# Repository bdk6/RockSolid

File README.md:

# RockSolid
Oven controlled quartz oscillator(s).

RockSolid is a cheap, easy to build, custom Oven Controlled Crystal
Oscillator (OCXO.)  You can build it for under $10 US, including having
the PCB made.  You can build it for the exact frequency you need.

## Credit
A significant amount of credit goes to someone on the web that I can't
find again.  I was in the process of designing a "simple" crystal oven
thought about doing something similar to how RockSolid works.  But what
I had was still considerably more complicated.  I found this basic circuit
on the web and was impressed.  I modified it a small amount and used it
in RockSolid.  As soon as I can find the website and name, I will be sure
to update that here.

## What's an OXCO and why do we need it?
Quartz crystal oscillators are known for being accurate.  And they are.
But, in general, not nearly as most people might think.  Go to your
favorite parts distributor website and look at crystals.  Under "tolerance"
you will find various numbers mostly from about 10 to 100 ppm.  That's
"Parts Per Million."  Let's settle on 100 for this discussion.  For each
one million "parts" there can be a variation of plus or minus 100.  In our
case the "parts" are "Hertz" of the oscillation.  For a 1 MHz crystal, the
error could be plus or minus 100 Hz.  For a 2 MHz crystal, it could be
2 times 100, or plus or minus 200 Hz.  Even though this way of specifying
it is a bit confusing at first, it turns out to be convenient.  It is, in
essence, another way of saying percentage.  Parts Per Million is a ratio,
 Parts / Million.  So, 100 ppm  is equal to 100 / 1,000,000 = 1/10,000
  = 0.01%.

It's imporant to remember that the specified 100 ppm is ONLY for the
crystal.  That means that the circuit can affect that even more.  But even
with a perfect circuit that doesn't add any more error (good luck!)
plugging in a different crystal can affect the frequency  as much as
200 ppm (remember it's plus or minus, so if the first one was plus 100
and the next was minus 100 the difference is 200 ppm.)  Of course, the
rest of the circuit is going to have its say, too.  So our error can be
considerably more than the crystal spec.

What does 100ppm mean in the real world?  It sounds pretty small.  Will
we even notice?  Let's take two examples.  A clock and a radio.

Let's build a "thought experiment" clock.  We start with a 1 MHz crystal
and divide it down to 1 Hz to count seconds.  There are 86400
(60 sec/min * 60 min/hr * 24 hr / day) in a day.  In a 30 day month, there
are 30 * 86400 or 2,592,000 seconds.

But our crystal is "fast" by 100 ppm.  So instead of 1,000,000 oscillations
per second it actually oscillates 1,000,100 times per second.  When we
divide that by 1,000,000 to get 1 Hz, we actually get 1.0001 Hz.  Doesn't
look like much, does it.  But, what we think is 1 second is actually
1/1.0001 second.  And if we count 86,400 of those for a day, we get
86,400 over 1.0001 seconds, which is about 86,391 seconds.  At the end of
one day our clock is off by almost 9 seconds!  How about a month?  Let's
divide 2,592,000 / 1.0001 = 2,591,740.  After a month our clock is off by
260 seconds!  Two minutes and 20 seconds!  A good quality, ancient,
wind-up wristwatch was often better than that.  And after a year it will
be off by over half an hour.  Maybe not so accurate.

How about a radio?  A "two meter" (144 to 148 MHz) amateur band fm radio
uses "channels" that are spaced 5 KHz apart.  Let's say we build a
crystal oscillator to work on the channel from 145,000,000 to 145,005,000
Hz.  We use a crystal at 145,000,000 Hz (those don't really exist, but
let's pretend they do.)  It is spec'ed as +- 100 ppm.  At 145 million Hz
that means plus or minus 145 * 100 = 14,500 Hz!  We could be in any one of
SIX different channels other than the one we intend!  Anywhere from
144,985,500 to 145,014,500 Hz!

So, what do we do?  First, buy a better crystal.  But don't go overboard.
They get expensive pretty quick and that still won't solve the problem
completely.  Keep in mind there are two different specs on the crystal.
One is the tolerance, which means in a perfect circuit it could be off
that much.  The other is stability.  Once you get it working how much
will the frequency vary over time.
Take a look at the datasheet for any decent quality crystal
that you can find.  There will usually be a graph showing frequency vs
temperature.  It will be an upside down parabola, with the peak at
some particular temperature.  That peak will usually be right at the
specified frequency.

So we see that the crystal frequency varies with temperature.  If we get
everything else set just right and keep the crystal temperature regulated,
we can make it quite accurate and stable.  The peak of that parabola,
though, is usually specified at 25 C.  That's about room temperature.  Do
we need a heater and air conditioner?  Not necessarily.

There are other factors.  I've alluded to them a few times.  The frequency
the crystal oscillates at has a lot to do with the circuit it is in.
Especially the capacitance of that circuit.  We can vary the capacitance
of the circuit and adjust the frequency.  We can usually cover a pretty
wide range of frequencies that way.  Heating a circuit is pretty easy;
we do that all the time, like it or not.  Cooling is not so easy.  So,
let's heat the circuit up to some temperature above anything it might
encounter naturally.  Say 35 to 40 C.  And keep it stable.  Now, adjust
the rest of the circuit right on frequency at that temperature.  It will
now be MUCH more stable.  The better the quality of the components used,
the more stable and accurate it will be.  But even with rather cheap
parts it will be drastically improved.  You won't get NIST lab quality
from a ten cent crystal and cheap ebay capacitors, but you can get to or
below 1 ppm!

This temperature controlled oscillator is called an Oven Controlled
Crystal Oscillator or OXCO.

And THAT is what RockSolid is all about.  It's a crystal oscillator and
temperature regulating circuit, housed in a well-insulated environment
to get decent accuracy from a crystal oscillator.

## History

## The Goal and the Circuit
My ultimate goal for this project is a 0.1 frequency reference.  With
good quality parts and some work, I think that's achievable.  We'll see.
Even with really cheap parts from Chinal totalling less than $2 I think
we can get 1 ppm.  And this is small and cheap enough to build that you
can use it in various projects without adding much cost or too much space.
One ppm is often plenty good enough.  It gets you a clock accurate to
better than 3 seconds a month.  Or a radio that's close enough on
frequency.  Or a frequency counter that's off by no more than 10 Hz when
measuring a 10 Mhz signal.  It would have been considered lab quality
not TOO long ago.

The circuit is simple and cheap.  A standard 74HC04 CMOS hex inverter is
used as the active device.  The crystal and its capacitors are added
to build an oscillator.  The voltage to the oscillator is regulated
internally by a 78L05 regulator kept at the same temperature.  Voltage
will affect the frequency, too.  By keeping the regulator temperature
regulated, it is much more accurate.  For the same reason, it has a
near-constant load.  So the 5V may be off a little, but it should stay
quite stable.  Stability is the key.  We can adjust for inaccuracy, as
long as it stays stable.  The heater circuit consists of a power MOSFET
and two power resistors as heaters.  The MOSFET is controlled by a
divider circuit with a potentiometer and a thermistor.  As the thermistor
heats up, it cuts down drive to the MOSFET, decreasing the heating.  As
it cools, it increases the drive and heating.  The feedback stabilizes
the temperature, and we build the whole thing to spread the heat evenly
and be well-insulated from the outside world.  The heater and five volt
regulator are fed from an external, regulated 12 volt supply.

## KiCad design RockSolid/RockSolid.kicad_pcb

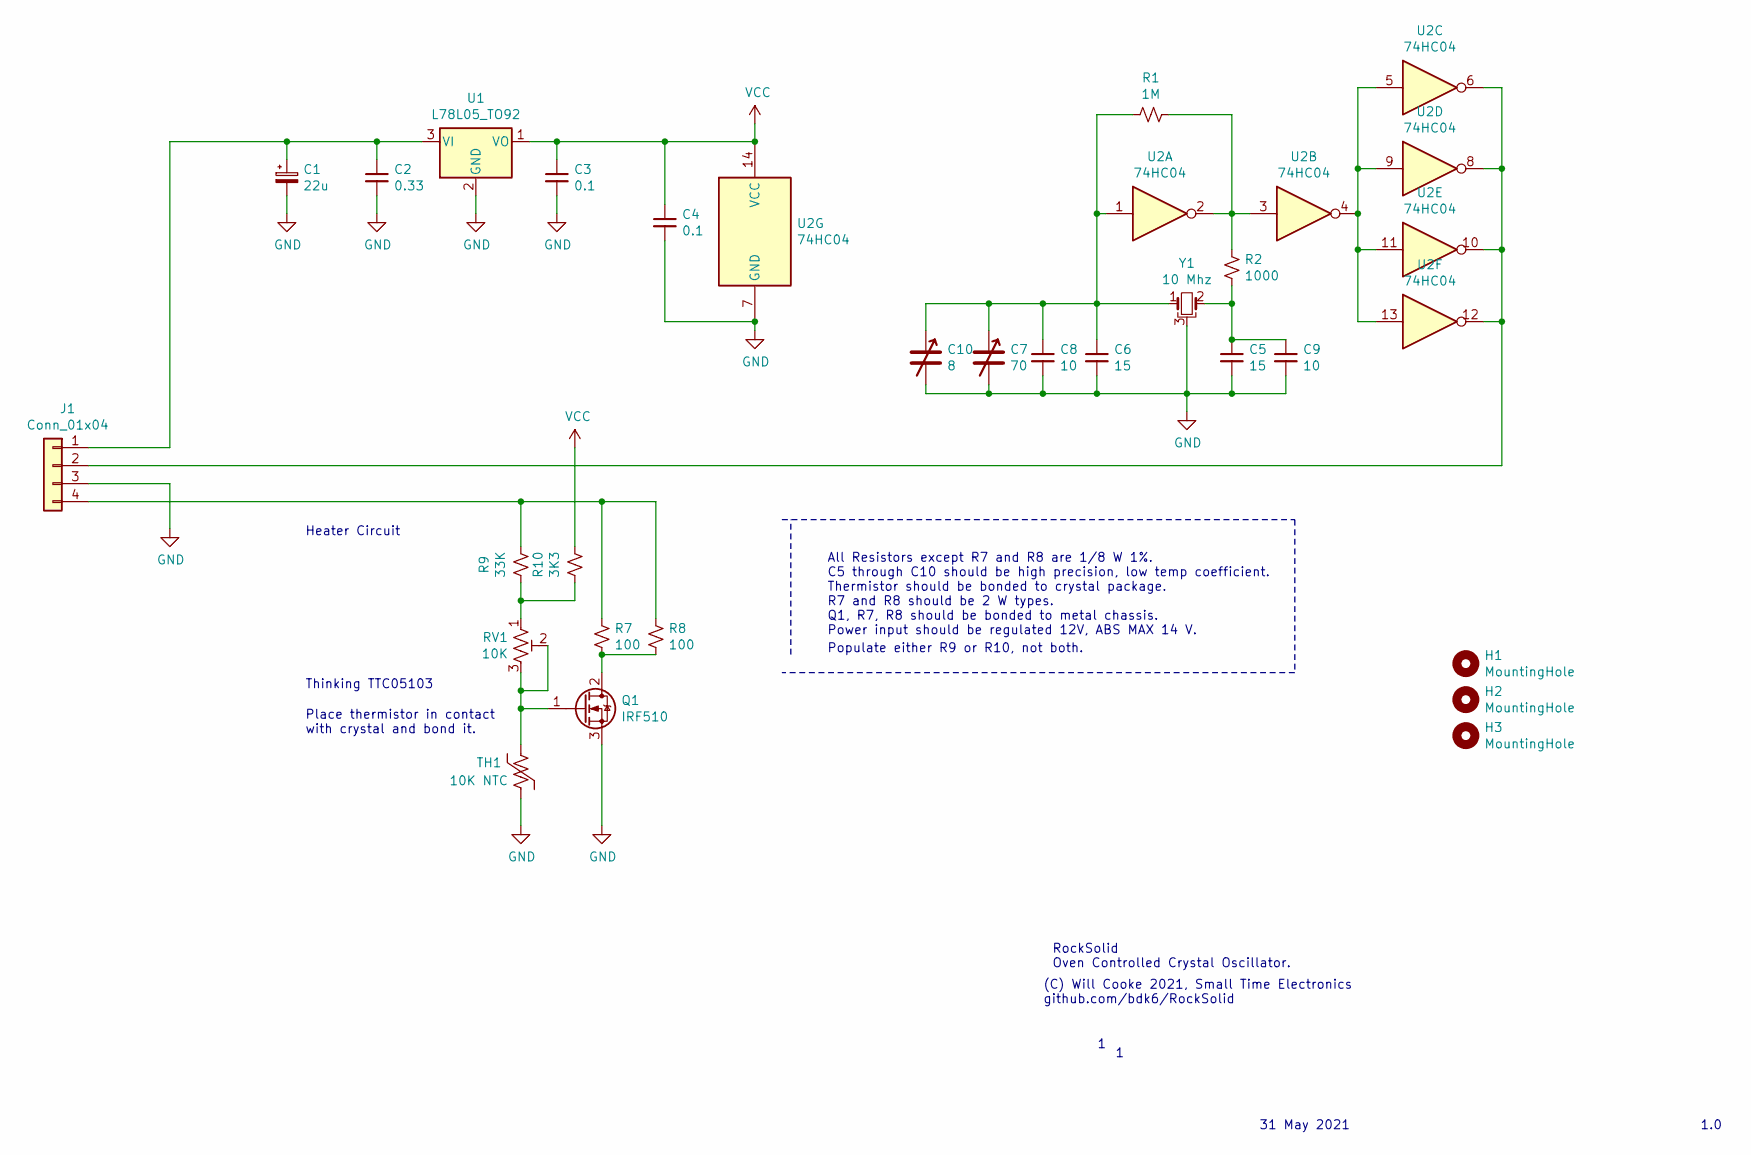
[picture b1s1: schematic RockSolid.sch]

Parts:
C1: 22u; CP_Radial_D5.0mm_P2.00mm
C2: 0.33; C_Disc_D4.7mm_W2.5mm_P5.00mm
C3, C4: 0.1; C_Disc_D4.7mm_W2.5mm_P5.00mm
C5, C6: 15; C_Disc_D4.7mm_W2.5mm_P5.00mm
C7: 70; C_Trimmer_6mm_2pin_5mm
C8, C9: 10; C_Disc_D4.7mm_W2.5mm_P5.00mm
C10: 8; C_Trimmer_6mm_2pin_5mm
H1, H2, H3: MountingHole; MountingHole_2.5mm
J1: Conn_01x04; PinHeader_1x04_P2.54mm_Vertical
Q1: IRF510; TO-220-3_Vertical
R1: 1M; R_Axial_DIN0207_L6.3mm_D2.5mm_P7.62mm_Horizontal
R2: 1000; R_Axial_DIN0207_L6.3mm_D2.5mm_P7.62mm_Horizontal
R7, R8: 100; R_Axial_DIN0617_L17.0mm_D6.0mm_P7.62mm_Vertical
R9: 33K; R_Axial_DIN0207_L6.3mm_D2.5mm_P7.62mm_Horizontal
R10: 3K3; R_Axial_DIN0207_L6.3mm_D2.5mm_P7.62mm_Horizontal
RV1: 10K; Potentiometer_ACP_CA9-H5_Horizontal
TH1: 10K NTC; R_Axial_DIN0207_L6.3mm_D2.5mm_P5.08mm_Vertical
U1: L78L05_TO92; TO-92_Inline
U2: 74HC04; DIP-14_W7.62mm
Y1: 10 Mhz; Crystal_HC49-U_Horizontal_1EP_style2

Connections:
GND: C1.2, C2.2, C3.2, C4.2, C5.2, C6.2, C7.2, C8.2, C9.2, C10.2, J1.3, Q1.3 (S), TH1.2, U1.2 (GND), U2.7 (GND), Y1.3
unnamed: C1.1, C2.1, J1.1, U1.3 (VI)
unnamed: C5.1, C9.1, R2.2, Y1.2
unnamed: C6.1, C7.1, C8.1, C10.1, R1.2, U2.1, Y1.1
unnamed: J1.2, U2.6, U2.8, U2.10, U2.12
unnamed: J1.4, R7.1, R8.1, R9.1
unnamed: Q1.1 (G), RV1.2, RV1.3, TH1.1
unnamed: Q1.2 (D), R7.2, R8.2
unnamed: R1.1, R2.1, U2.2, U2.3
unnamed: R9.2, R10.2, RV1.1
unnamed: U2.4, U2.5, U2.9, U2.11, U2.13
VCC: C3.1, C4.1, R10.1, U1.1 (VO), U2.14 (VCC)

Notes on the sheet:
Thinking TTC05103
Heater Circuit
Place thermistor in contact with crystal and bond it.
1.0
31 May 2021
RockSolid Oven Controlled Crystal Oscillator.
(C) Will Cooke 2021, Small Time Electronics github.com/bdk6/RockSolid
All Resistors except R7 and R8 are 1/8 W 1%. C5 through C10 should be high precision, low temp coefficient. Thermistor should be bonded to crystal package. R7 and R8 should be 2 W types. Q1, R7, R8 should be bonded to metal chassis. Power input should be regulated 12V, ABS MAX 14 V.
Populate either R9 or R10, not both.

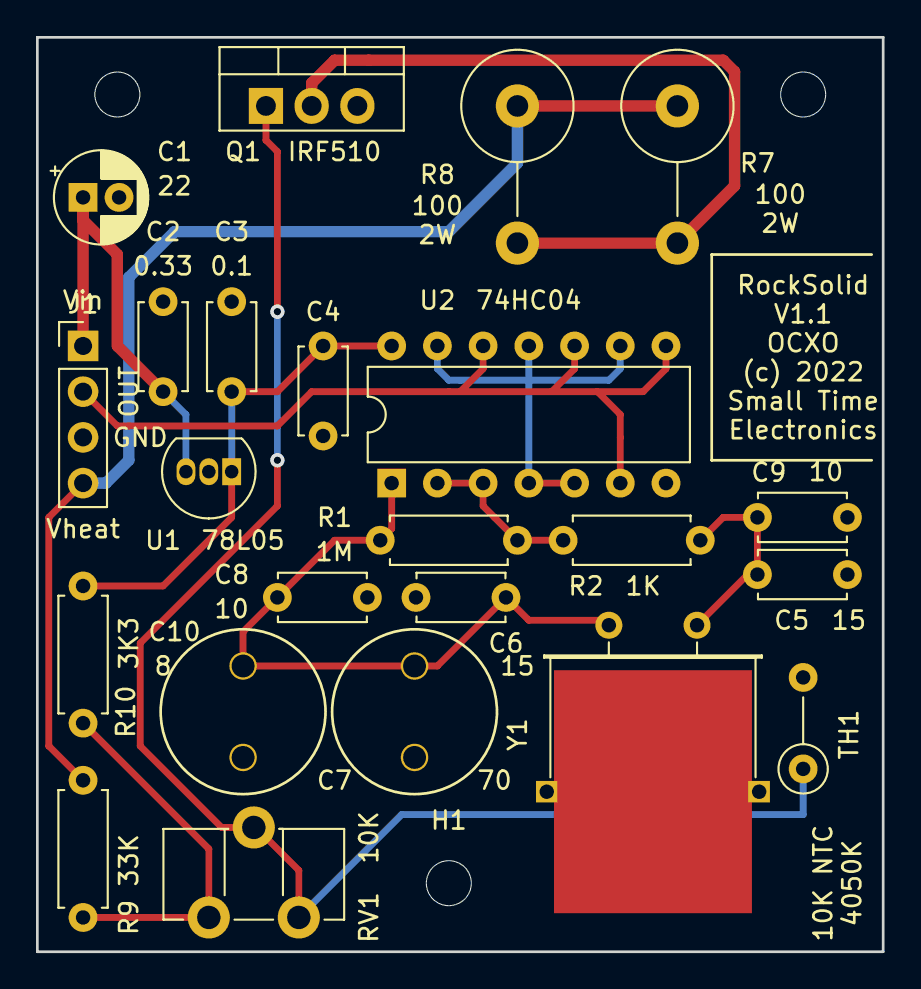
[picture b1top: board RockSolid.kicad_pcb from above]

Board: 2 copper layers, 47.0 x 50.8 mm, 26 parts (0 on the bottom side), 12 nets.

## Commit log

2021-05-31 Added schematic and cad files
2021-06-01 Finished schematic, initial board layout
2022-09-08 Initial version before changes.
2022-09-10 Version 1.0RC1 complete.
2022-09-10 OK, NOW ver 1.0 RC1 complete.
2022-09-10 v1.0 RC1 gerbers generated.
2022-09-10 Added gerbers zip file.
2022-10-01 v1.01 added labels on PCB, grounded crystal, silkscreen updates.

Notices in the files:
RockSolid/RockSolid.kicad_pcb:
(c) 2022
(c) 2022 Will Cooke
